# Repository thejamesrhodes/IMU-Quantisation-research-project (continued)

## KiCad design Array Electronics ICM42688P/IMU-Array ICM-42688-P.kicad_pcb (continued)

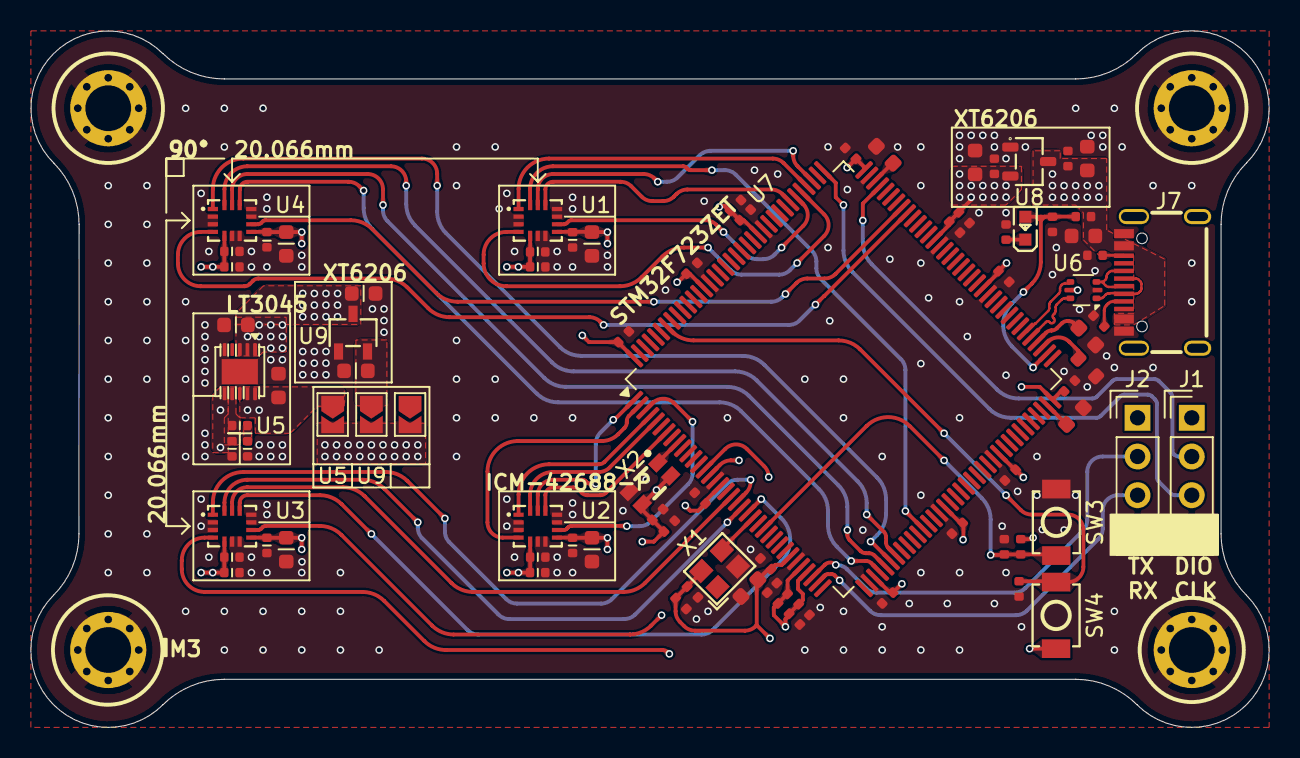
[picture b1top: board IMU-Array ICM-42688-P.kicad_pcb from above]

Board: 4 copper layers, 81.3 x 45.7 mm, 87 parts (0 on the bottom side), 52 nets.

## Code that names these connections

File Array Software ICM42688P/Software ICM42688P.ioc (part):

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Mcu.Name=STM32F723Z(C-E)Tx
Mcu.Package=LQFP144
Mcu.UserName=STM32F723ZETx
PA0-WKUP.GPIOParameters=GPIO_Label
PA0-WKUP.GPIO_Label=TX
PA0-WKUP.Mode=Asynchronous
PA0-WKUP.Signal=UART4_TX
PA1.GPIOParameters=GPIO_Label
PA1.GPIO_Label=RX
PA1.Mode=Asynchronous
PA1.Signal=UART4_RX
PA13.GPIOParameters=GPIO_Label
PA13.GPIO_Label=SWDIO
PA13.Mode=Serial_Wire
PA13.Signal=SYS_JTMS-SWDIO
PA14.GPIOParameters=GPIO_Label
PA14.GPIO_Label=SWCLK
PA14.Mode=Serial_Wire
PA14.Signal=SYS_JTCK-SWCLK
PA4.GPIOParameters=GPIO_Label
PA4.GPIO_Label=CS_1
PA4.Signal=GPIO_Output
PA5.GPIOParameters=GPIO_Label
PA5.GPIO_Label=SCK_1
PA5.Mode=Full_Duplex_Master
PA5.Signal=SPI1_SCK
PA6.GPIOParameters=GPIO_Label
PA6.GPIO_Label=MISO_1
PA6.Mode=Full_Duplex_Master
PA6.Signal=SPI1_MISO
PA7.GPIOParameters=GPIO_Label
PA7.GPIO_Label=MOSI_1
PA7.Mode=Full_Duplex_Master
PA7.Signal=SPI1_MOSI
PB13.GPIOParameters=GPIO_Label
PB13.GPIO_Label=VBUS
PB13.Mode=Activate_VBUS_FS
PB13.Signal=USB_OTG_HS_VBUS
PB14.GPIOParameters=GPIO_Label
PB14.GPIO_Label=USB_D-
PB14.Mode=Internal_Phy_Device
PB14.Signal=USB_OTG_HS_DM
PB15.GPIOParameters=GPIO_Label
PB15.GPIO_Label=USB_D+
PB15.Mode=Internal_Phy_Device
PB15.Signal=USB_OTG_HS_DP
PB2.GPIOParameters=GPIO_Label
PB2.GPIO_Label=MOSI_2
PB2.Mode=Full_Duplex_Master
PB2.Signal=SPI3_MOSI
PC10.GPIOParameters=GPIO_Label
PC10.GPIO_Label=SCK_2
PC10.Mode=Full_Duplex_Master
PC10.Signal=SPI3_SCK
PC11.GPIOParameters=GPIO_Label
PC11.GPIO_Label=MISO_2
PC11.Mode=Full_Duplex_Master
PC11.Signal=SPI3_MISO
PC12.GPIOParameters=GPIO_Label
PC12.GPIO_Label=INT2.1
PC12.Signal=GPIO_Input
PC14-OSC32_IN.GPIOParameters=GPIO_Label
PC14-OSC32_IN.GPIO_Label=IN_LSE
PC14-OSC32_IN.Mode=LSE-External-Clock-Source
PC14-OSC32_IN.Signal=RCC_OSC32_IN
PC15-OSC32_OUT.GPIOParameters=GPIO_Label
PC15-OSC32_OUT.GPIO_Label=OUT_LSE
PC15-OSC32_OUT.Mode=LSE-External-Clock-Source
PC15-OSC32_OUT.Signal=RCC_OSC32_OUT
PC4.GPIOParameters=GPIO_Label
PC4.GPIO_Label=INT1.1
PC4.Signal=GPIO_Input
PC5.GPIOParameters=GPIO_Label
PC5.GPIO_Label=INT1.2
PC5.Signal=GPIO_Input
PD0.GPIOParameters=GPIO_Label
PD0.GPIO_Label=INT2.2
PD0.Signal=GPIO_Input
PD1.GPIOParameters=GPIO_Label
PD1.GPIO_Label=CS_2
PD1.Signal=GPIO_Output
PE2.GPIOParameters=GPIO_Label
PE2.GPIO_Label=SCK_4
PE2.Mode=Full_Duplex_Master
PE2.Signal=SPI4_SCK
PE3.GPIOParameters=GPIO_Label
PE3.GPIO_Label=INT4.1
PE3.Signal=GPIO_Input
PE4.GPIOParameters=GPIO_Label
PE4.GPIO_Label=INT4.2
PE4.Signal=GPIO_Input
PE5.GPIOParameters=GPIO_Label
PE5.GPIO_Label=MISO_4
PE5.Mode=Full_Duplex_Master
PE5.Signal=SPI4_MISO
PE6.GPIOParameters=GPIO_Label
PE6.GPIO_Label=MOSI_4
PE6.Mode=Full_Duplex_Master
PE6.Signal=SPI4_MOSI
PE7.GPIOParameters=GPIO_Label
PE7.GPIO_Label=CS_4
PE7.Signal=GPIO_Output
PF10.GPIOParameters=GPIO_Label
PF10.GPIO_Label=CS_3
PF10.Signal=GPIO_Output
PF4.GPIOParameters=GPIO_Label
PF4.GPIO_Label=INT3.2
PF4.Signal=GPIO_Input
PF5.GPIOParameters=GPIO_Label
PF5.GPIO_Label=INT3.1
PF5.Signal=GPIO_Input
PF7.GPIOParameters=GPIO_Label
PF7.GPIO_Label=SCK_3
PF7.Mode=Full_Duplex_Master
PF7.Signal=SPI5_SCK
PF8.GPIOParameters=GPIO_Label
PF8.GPIO_Label=MISO_3
PF8.Mode=Full_Duplex_Master
PF8.Signal=SPI5_MISO
PF9.GPIOParameters=GPIO_Label
PF9.GPIO_Label=MOSI_3
PF9.Mode=Full_Duplex_Master
PF9.Signal=SPI5_MOSI
PH0-OSC_IN.GPIOParameters=GPIO_Label
PH0-OSC_IN.GPIO_Label=IN_HSE
PH0-OSC_IN.Mode=HSE-External-Clock-Source
PH0-OSC_IN.Signal=RCC_OSC_IN
PH1-OSC_OUT.GPIOParameters=GPIO_Label
PH1-OSC_OUT.GPIO_Label=OUT_HSE
PH1-OSC_OUT.Mode=HSE-External-Clock-Source
PH1-OSC_OUT.Signal=RCC_OSC_OUT
RCC.HSE_VALUE=24000000
RCC.SYSCLKFreq_VALUE=216000000
RCC.SYSCLKSource=RCC_SYSCLKSOURCE_PLLCLK
board=custom
